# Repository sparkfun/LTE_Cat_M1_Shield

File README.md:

SparkFun LTE CAT M1/NB-IoT Shield - SARA-R4
========================================

[*SparkFun LTE CAT M1/NB-IoT Shield - SARA-R4 (CEL-14997)*](https://www.sparkfun.com/products/14997)

Arduino shield featuring a SARA-R410M-02B module, which supports both Cat M1 and NB-IoT

Repository Contents
-------------------

* **/Documentation** - Data sheets, additional product information
* **/Hardware** - Eagle design files (.brd, .sch)
* **/Production** - Production panel files (.brd)

Documentation
--------------
* **[Installing an Arduino Library Guide](https://learn.sparkfun.com/tutorials/installing-an-arduino-library)** - Basic information on how to install an Arduino library.
* **[Library](https://github.com/sparkfun/SparkFun_LTE_Shield_Arduino_Library)** - Arduino library.
* **[Hookup Guide](https://learn.sparkfun.com/tutorials/lte-cat-m1nb-iot-shield-hookup-guide)** - Basic hookup guide.

Version History
---------------
* v11 - Removed `GND` connection to `AREF` pin
* [v10](https://github.com/sparkfun/LTE_Cat_M1_Shield/releases/tag/v10) - Initial Release

License Information
-------------------

This product is _**open source**_! 

Various bits of the code have different licenses applied. Anything SparkFun wrote is beerware; if you see me (or any other SparkFun employee) at the local, and you've found our code helpful, please buy us a round!

Please use, reuse, and modify these files as you see fit. Please maintain attribution to SparkFun Electronics and release anything derivative under the same license.

Distributed as-is; no warranty is given.

- Your friends at SparkFun.

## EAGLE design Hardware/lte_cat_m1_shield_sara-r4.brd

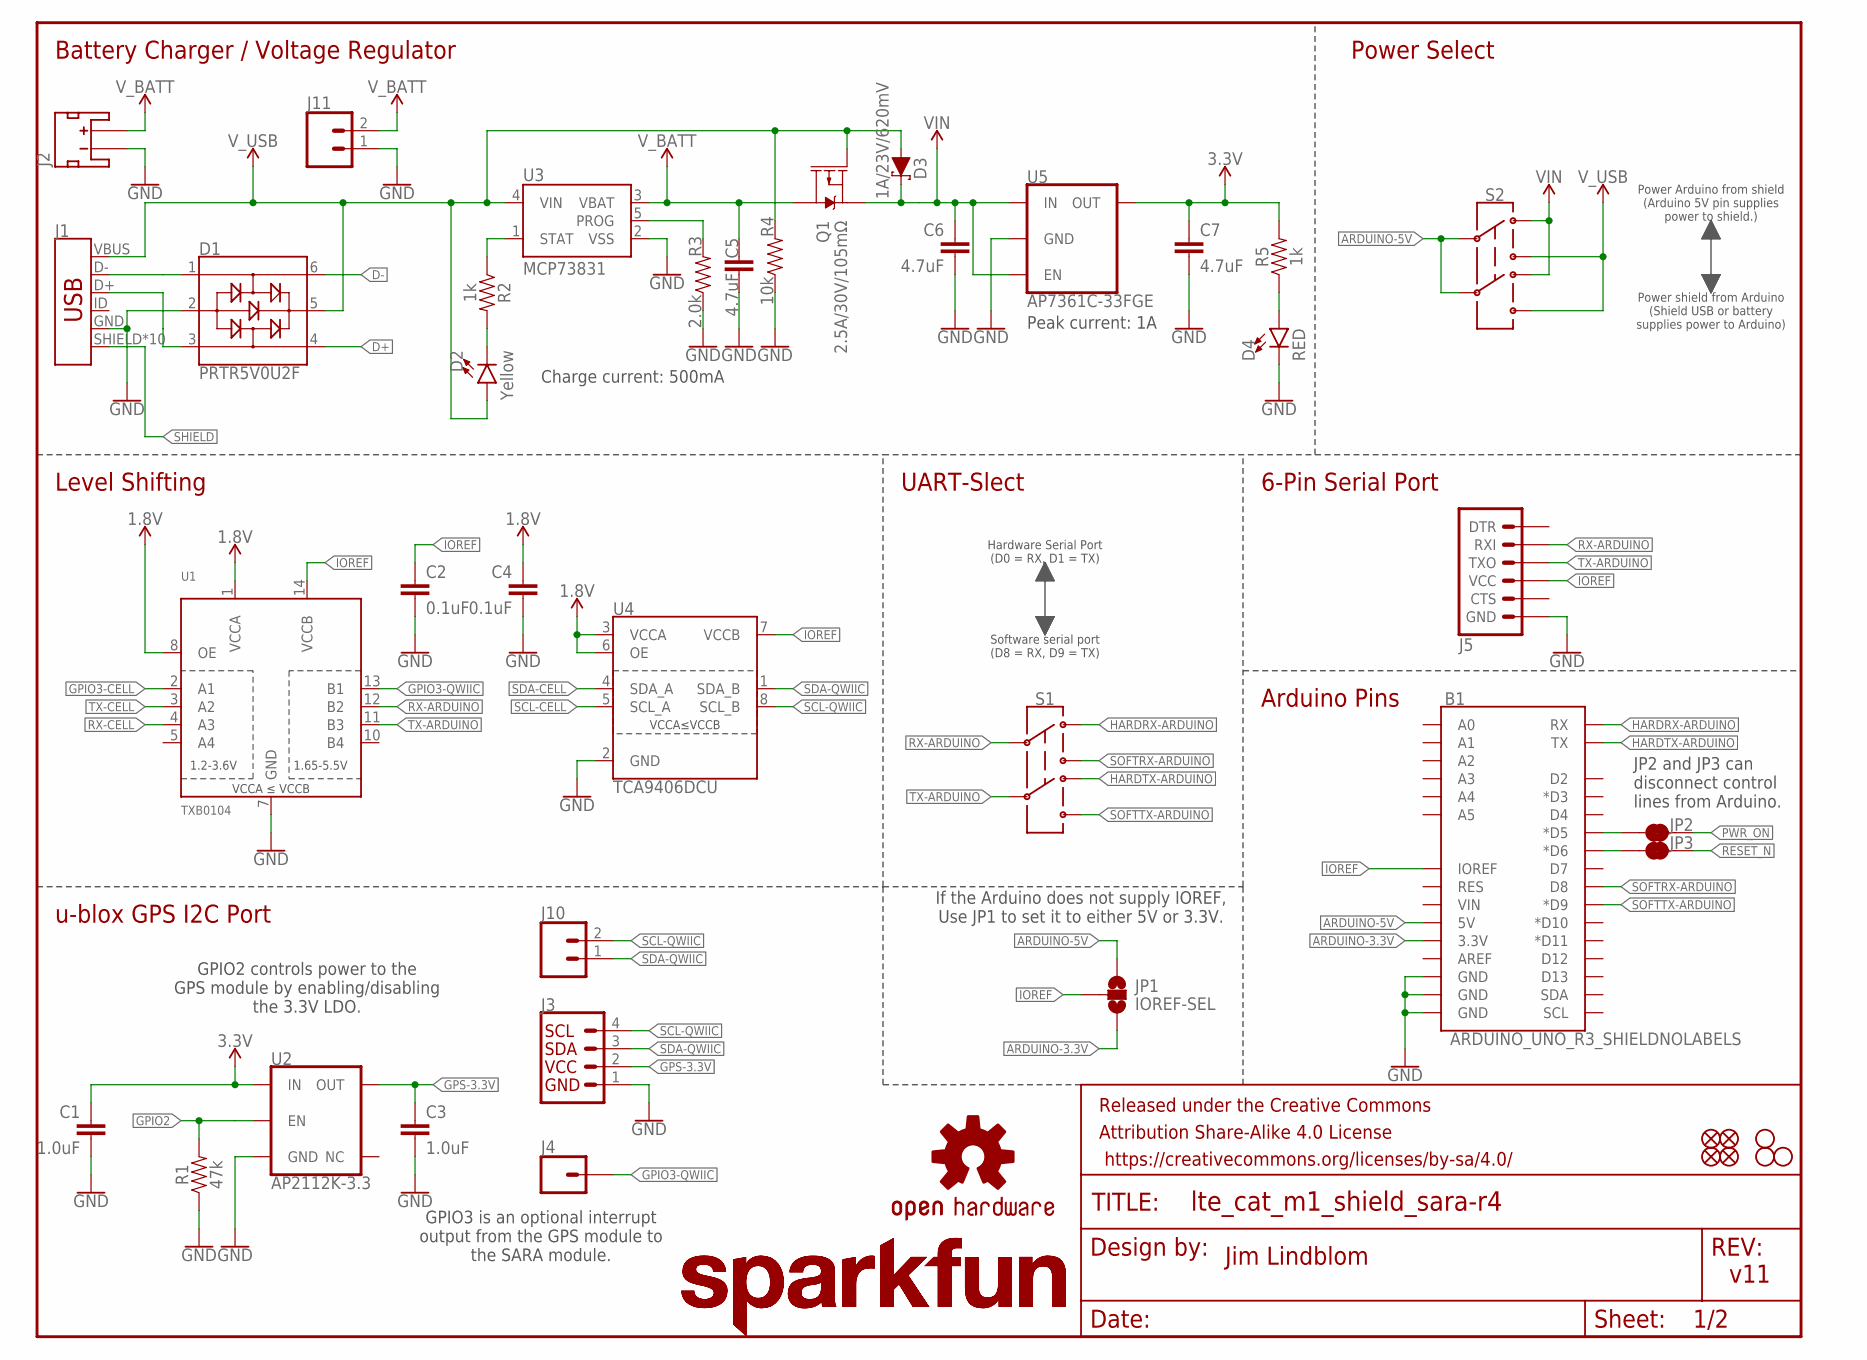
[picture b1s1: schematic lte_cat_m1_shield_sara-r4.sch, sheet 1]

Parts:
B1: ARDUINO_UNO_R3_SHIELDNOLABELS; UNO_R3_SHIELD_NOLABELS
C1, C3: 1.0uF; 0603
C2, C4: 0.1uF; 0603
C5, C6, C7: 4.7uF; 0603
D1: PRTR5V0U2F; SOT886
D2: Yellow; LED-0603
D3: 1A/23V/620mV; SOD-323
D4: RED; LED-0603
FD1, FD2, FD3, FD4: FIDUCIALUFIDUCIAL; FIDUCIAL-MICRO
FRAME1: FRAME-LETTER; CREATIVE_COMMONS
H1, H2, H3: STAND-OFF
J1: USB_MICRO-B_HALF_PTH_MILL; USB-MICROB-PTH-MILL
J2: JST_2MM_MALESMD; JST-2-SMD
J3: QWIIC_CONNECTORJS-1MM; 1X04_1MM_RA
J4: CONN_01PTH_NO_SILK_YES_STOP; 1X01_NO_SILK
J5: 6_PIN_SERIAL_TARGETNO_SILK; 1X06_NO_SILK
J10, J11: CONN_021X02_NO_SILK; 1X02_NO_SILK
JP1: IOREF-SEL; SMT-JUMPER_3_NO_SILK
JP2, JP3: JUMPER-SMT_2_NC_TRACE_SILK; SMT-JUMPER_2_NC_TRACE_SILK
LOGO1, LOGO3: SFE_LOGO_NAME.2_INCH; SFE_LOGO_NAME_.2
LOGO2: OSHW-LOGOM; OSHW-LOGO-M
Q1: 2.5A/30V/105mΩ; SOT23-3
R1: 47k; 0603
R2, R5: 1k; 0603
R3: 2.0k; 0603
R4: 10k; 0603
S1, S2: SWITCH-DPDT-SMD-AYZ0202; SWITCH_DPDT_SMD_AYZ0202
U1: TXB0104; TSSOP14
U2: AP2112K-3.3; SOT23-5
U3: MCP73831; SOT23-5
U4: TCA9406DCU; VSSOP-8
U5: AP7361C-33FGE; 8-UDFN

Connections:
1.8V: C4.1, U1.1 (VCCA), U1.8 (OE), U4.3 (VCCA), U4.6 (OE); also elsewhere on the board
3.3V: C1.1, C7.1, R5.2, U2.1 (IN), U5.1 (OUT); also elsewhere on the board
ARDUINO-3.3V: B1.3.3V, JP1.3
ARDUINO-5V: B1.5V, JP1.1, S2.2, S2.5
D+: D1.4; also elsewhere on the board
D-: D1.6; also elsewhere on the board
GND: B1.GND@0 (GND), B1.GND@1 (GND), B1.GND@2 (GND), C1.2, C2.2, C3.2, C4.2, C5.2, C6.2, C7.2, D1.2, D4.C, J1.GND, J2.1 (-), J3.1, J5.6 (GND), J11.1, R1.1, R3.1, R4.1, U1.7 (GND), U2.2 (GND), U3.2 (VSS), U4.2 (GND), U5.4 (GND), U5.EP (GND); also elsewhere on the board
GPIO2: R1.2, U2.3 (EN); also elsewhere on the board
GPIO3-CELL: U1.2 (A1); also elsewhere on the board
GPIO3-QWIIC: J4.1, U1.13 (B1)
GPS-3.3V: C3.1, J3.2, U2.5 (OUT)
HARDRX-ARDUINO: B1.RX, S1.1
HARDTX-ARDUINO: B1.TX, S1.4
IOREF: B1.IOREF, C2.1, J5.4 (VCC), JP1.2, U1.14 (VCCB), U4.7 (VCCB)
unnamed: R3.2, U3.5 (PROG)
unnamed: D1.1, J1.D-
unnamed: D1.3, J1.D+
unnamed: D4.A, R5.1
unnamed: D2.C, R2.2
unnamed: R2.1, U3.1 (STAT)
unnamed: B1.D5 (*D5), JP2.1
unnamed: B1.D6 (*D6), JP3.1
PWR_ON: JP2.2; also elsewhere on the board
RESET_N: JP3.2; also elsewhere on the board
RX-ARDUINO: J5.2 (RXI), S1.2, U1.12 (B2)
RX-CELL: U1.4 (A3); also elsewhere on the board
SCL-CELL: U4.5 (SCL_A); also elsewhere on the board
SCL-QWIIC: J3.4, J10.2, U4.8 (SCL_B)
SDA-CELL: U4.4 (SDA_A); also elsewhere on the board
SDA-QWIIC: J3.3, J10.1, U4.1 (SDA_B)
SHIELD: J1.SHIELD, J1.SHIELD2 (SHIELD), J1.SHIELD3 (SHIELD), J1.SHIELD4 (SHIELD), J1.SHIELD5 (SHIELD), J1.SHIELD6 (SHIELD), J1.SHIELD7 (SHIELD), J1.SHIELD8 (SHIELD), J1.SHIELD9 (SHIELD), J1.SHIELD10 (SHIELD)
SOFTRX-ARDUINO: B1.D8, S1.3
SOFTTX-ARDUINO: B1.D9 (*D9), S1.6
TX-ARDUINO: J5.3 (TXO), S1.5, U1.11 (B3)
TX-CELL: U1.3 (A2); also elsewhere on the board
VIN: C6.1, D3.C, Q1.2 (S), S2.1, S2.4, U5.5 (EN), U5.8 (IN)
V_BATT: C5.1, J2.2 (+), J11.2, Q1.3 (D), U3.3 (VBAT)
V_USB: D1.5, D2.A, D3.A, J1.VBUS, Q1.1 (G), R4.2, S2.3, S2.6, U3.4 (VIN); also elsewhere on the board

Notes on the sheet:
Charge current: 500mA
Power Arduino from shield (Arduino 5V pin supplies power to shield.)
Power shield from Arduino (Shield USB or battery supplies power to Arduino)
Battery Charger / Voltage Regulator
Power Select
Level Shifting
If the Arduino does not supply IOREF, Use JP1 to set it to either 5V or 3.3V.
u-blox GPS I2C Port
GPIO2 controls power to the GPS module by enabling/disabling the 3.3V LDO.
GPIO3 is an optional interrupt output from the GPS module to the SARA module.
UART-Slect
6-Pin Serial Port
Arduino Pins
Jim Lindblom
v11
Peak current: 1A
Hardware Serial Port (D0 = RX, D1 = TX)
Software serial port (D8 = RX, D9 = TX)
JP2 and JP3 can disconnect control lines from Arduino.

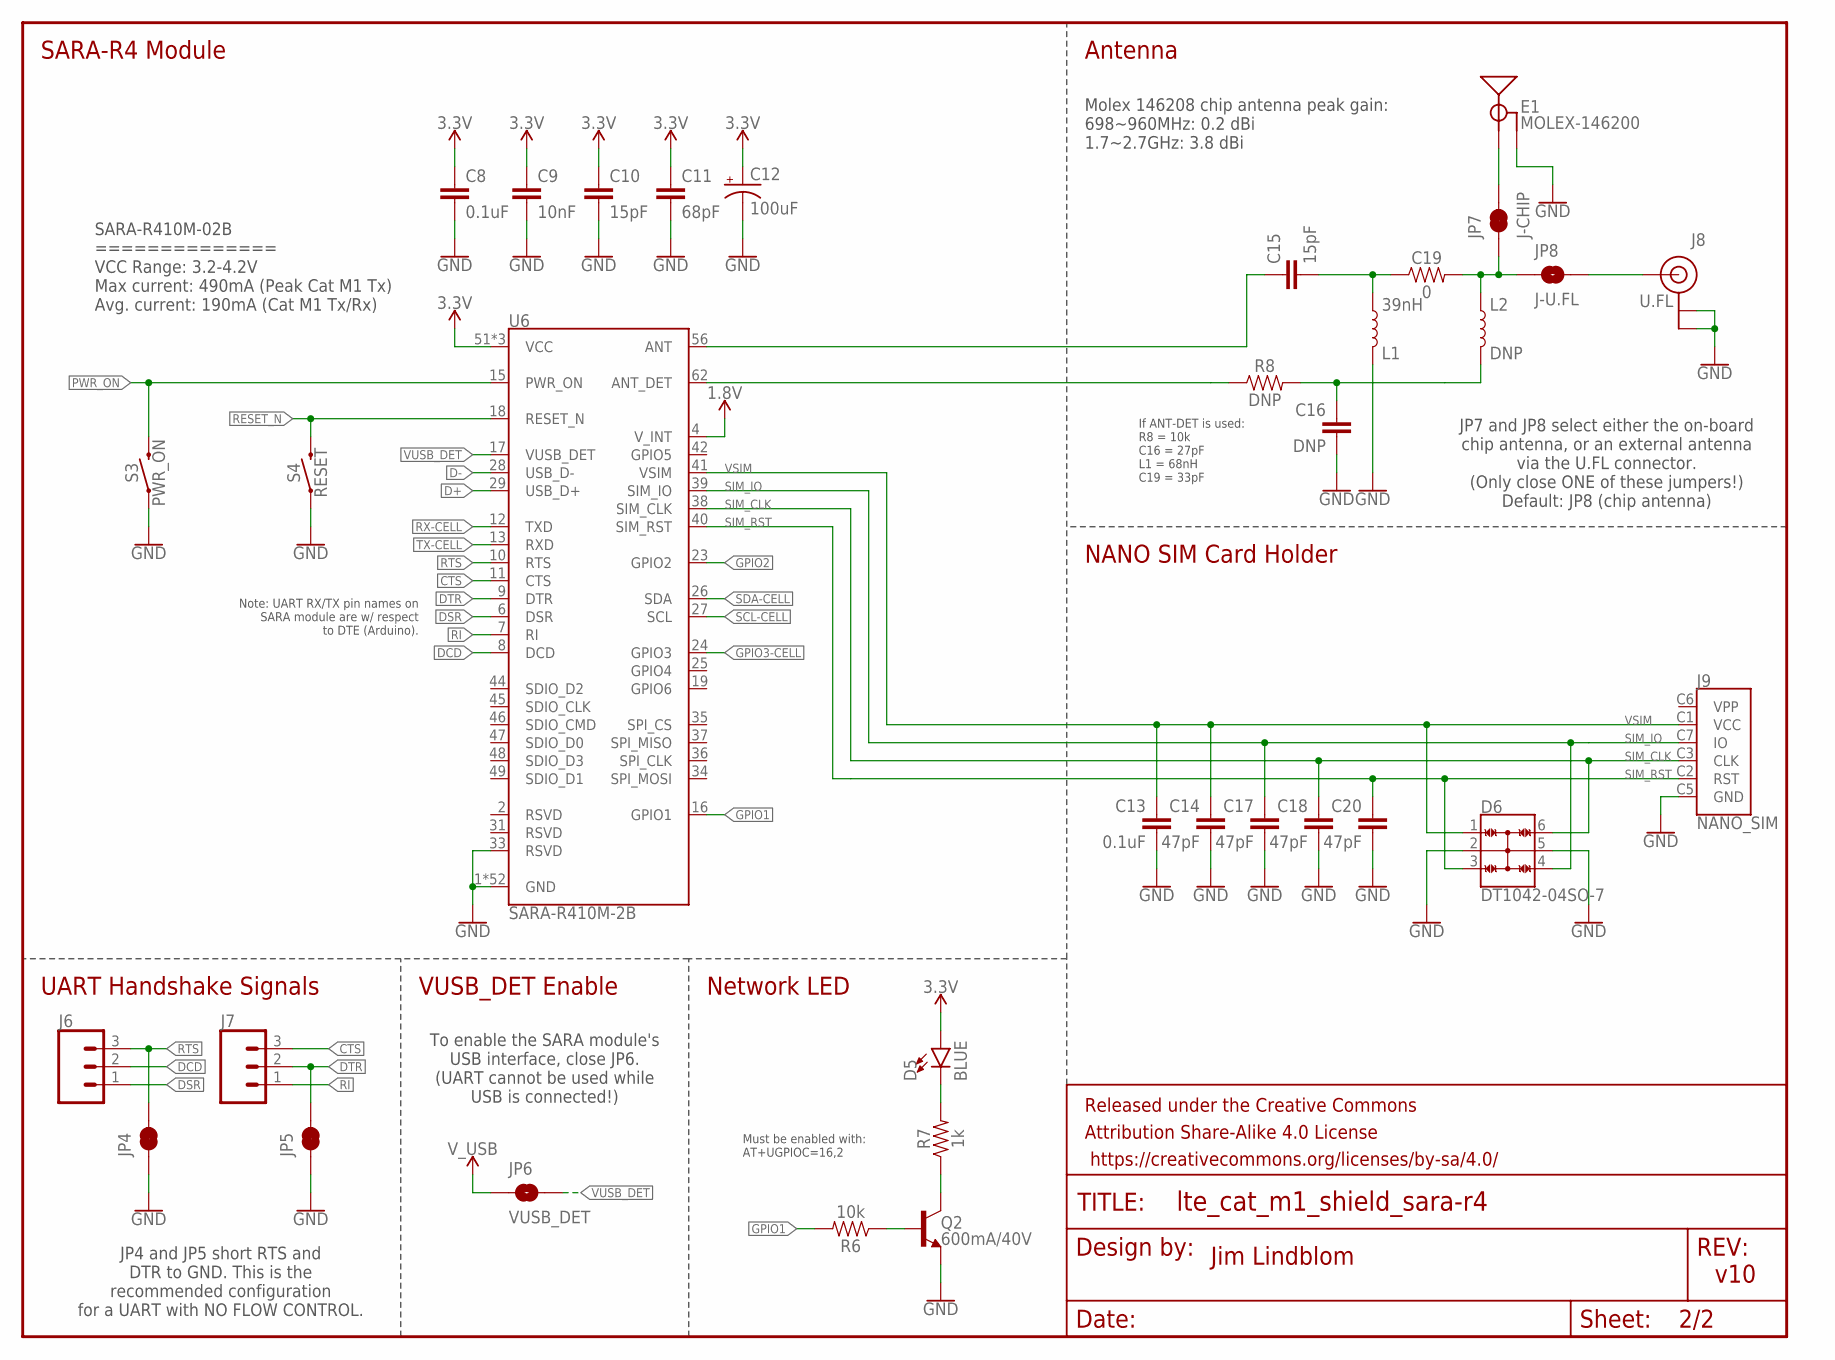
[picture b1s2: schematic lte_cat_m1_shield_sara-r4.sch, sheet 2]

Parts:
C8, C13: 0.1uF; 0603
C9: 10nF; 0603
C10, C15: 15pF; 0603
C11: 68pF; 0603
C12: 100uF; 1206-POLAR
C14, C17, C18, C20: 47pF; 0603
C16: DNP; 0603
C19: 0; 0603
D5: BLUE; LED-0603
D6: DT1042-04SO-7; SOT23-6L
E1: MOLEX-146200; MOLEX_146200
FRAME2: FRAME-LETTER; CREATIVE_COMMONS
J6, J7: CONN_031X03_NO_SILK; 1X03_NO_SILK
J8: U.FL
J9: NANO_SIM; NANO_SIM_WURTH_693043020611
JP4, JP5: JUMPER-SMT_2_NC_TRACE_SILK; SMT-JUMPER_2_NC_TRACE_SILK
JP6: VUSB_DET; SMT-JUMPER_2_NO_SILK
JP7: J-CHIP; SMT-JUMPER_2_NC_TRACE_NO-SILK
JP8: J-U.FL; SMT-JUMPER_2_NO_NO-SILK
L1: 39nH; 0603
L2: DNP; 0603
Q2: 600mA/40V; SOT23-3
R6: 10k; 0603
R7: 1k; 0603
R8: DNP; 0603
S3: PWR_ON; TACTILE_SWITCH_SMD_5.2MM
S4: RESET; TACTILE_SWITCH_SMD_5.2MM
U6: SARA-R410M-2B; SARA-LGA

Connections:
1.8V: U6.4 (V_INT); also elsewhere on the board
3.3V: C8.1, C9.1, C10.1, C11.1, C12.1 (+), D5.A, U6.51 (VCC), U6.52 (VCC), U6.53 (VCC); also elsewhere on the board
ANT: C15.1, U6.56 (ANT)
ANT_DET: R8.1, U6.62 (ANT_DET)
CTS: J7.3, U6.11 (CTS)
D+: U6.29 (USB_D+); also elsewhere on the board
D-: U6.28 (USB_D-); also elsewhere on the board
DCD: J6.2, U6.8 (DCD)
DSR: J6.1, U6.6 (DSR)
DTR: J7.2, JP5.2, U6.9 (DTR)
GND: C8.2, C9.2, C10.2, C11.2, C12.2 (-), C13.2, C14.2, C16.2, C17.2, C18.2, C20.2, D6.2, D6.5, E1.GND, J8.1 (GND), J8.2 (GND), J9.C5 (GND), JP4.1, JP5.1, L1.1, Q2.2 (E), S3.1, S3.2 (1), S4.1, S4.2 (1), U6.1 (GND), U6.3 (GND), U6.5 (GND), U6.14 (GND), U6.20 (GND), U6.21 (GND), U6.22 (GND), U6.30 (GND), U6.32 (GND), U6.33 (RSVD), U6.43 (GND), U6.50 (GND), U6.54 (GND), U6.55 (GND), U6.57 (GND), U6.58 (GND), U6.59 (GND), U6.60 (GND), U6.61 (GND), U6.63 (GND), U6.64 (GND), U6.65 (GND), U6.66 (GND), U6.67 (GND), U6.68 (GND), U6.69 (GND), U6.70 (GND), U6.71 (GND), U6.72 (GND), U6.73 (GND), U6.74 (GND), U6.75 (GND), U6.76 (GND), U6.77 (GND), U6.78 (GND), U6.79 (GND), U6.80 (GND), U6.81 (GND), U6.82 (GND), U6.83 (GND), U6.84 (GND), U6.85 (GND), U6.86 (GND), U6.87 (GND), U6.88 (GND), U6.89 (GND), U6.90 (GND), U6.91 (GND), U6.92 (GND), U6.93 (GND), U6.94 (GND), U6.95 (GND), U6.96 (GND); also elsewhere on the board
GPIO1: R6.2, U6.16 (GPIO1)
GPIO2: U6.23 (GPIO2); also elsewhere on the board
GPIO3-CELL: U6.24 (GPIO3); also elsewhere on the board
unnamed: C16.1, L2.2, R8.2
unnamed: C15.2, C19.1, L1.2
unnamed: J8.FEED (SIGNAL), JP8.2
unnamed: Q2.1 (B), R6.1
unnamed: D5.C, R7.2
unnamed: Q2.3 (C), R7.1
unnamed: C19.2, JP7.1, JP8.1, L2.1
unnamed: E1.FEED (SIGNAL), JP7.2
PWR_ON: S3.3 (2), S3.4 (2), U6.15 (PWR_ON); also elsewhere on the board
RESET_N: S4.3 (2), S4.4 (2), U6.18 (RESET_N); also elsewhere on the board
RI: J7.1, U6.7 (RI)
RTS: J6.3, JP4.2, U6.10 (RTS)
RX-CELL: U6.12 (TXD); also elsewhere on the board
SCL-CELL: U6.27 (SCL); also elsewhere on the board
SDA-CELL: U6.26 (SDA); also elsewhere on the board
SIM_CLK: C18.1, D6.6, J9.C3 (CLK), U6.38 (SIM_CLK)
SIM_IO: C17.1, D6.4, J9.C7 (IO), U6.39 (SIM_IO)
SIM_RST: C20.1, D6.3, J9.C2 (RST), U6.40 (SIM_RST)
TX-CELL: U6.13 (RXD); also elsewhere on the board
VSIM: C13.1, C14.1, D6.1, J9.C1 (VCC), U6.41 (VSIM)
VUSB_DET: JP6.2, U6.17 (VUSB_DET)
V_USB: JP6.1; also elsewhere on the board

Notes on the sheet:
Antenna
SARA-R4 Module
UART Handshake Signals
VUSB_DET Enable
Network LED
To enable the SARA module's USB interface, close JP6. (UART cannot be used while USB is connected!)
JP4 and JP5 short RTS and DTR to GND. This is the recommended configuration for a UART with NO FLOW CONTROL.
NANO SIM Card Holder
JP7 and JP8 select either the on-board chip antenna, or an external antenna via the U.FL connector. (Only close ONE of these jumpers!) Default: JP8 (chip antenna)
Note: UART RX/TX pin names on SARA module are w/ respect to DTE (Arduino).
Molex 146208 chip antenna peak gain: 698~960MHz: 0.2 dBi 1.7~2.7GHz: 3.8 dBi
Jim Lindblom
v10
Must be enabled with: AT+UGPIOC=16,2
SARA-R410M-02B ============== VCC Range: 3.2-4.2V Max current: 490mA (Peak Cat M1 Tx) Avg. current: 190mA (Cat M1 Tx/Rx)
If ANT-DET is used: R8 = 10k C16 = 27pF L1 = 68nH C19 = 33pF

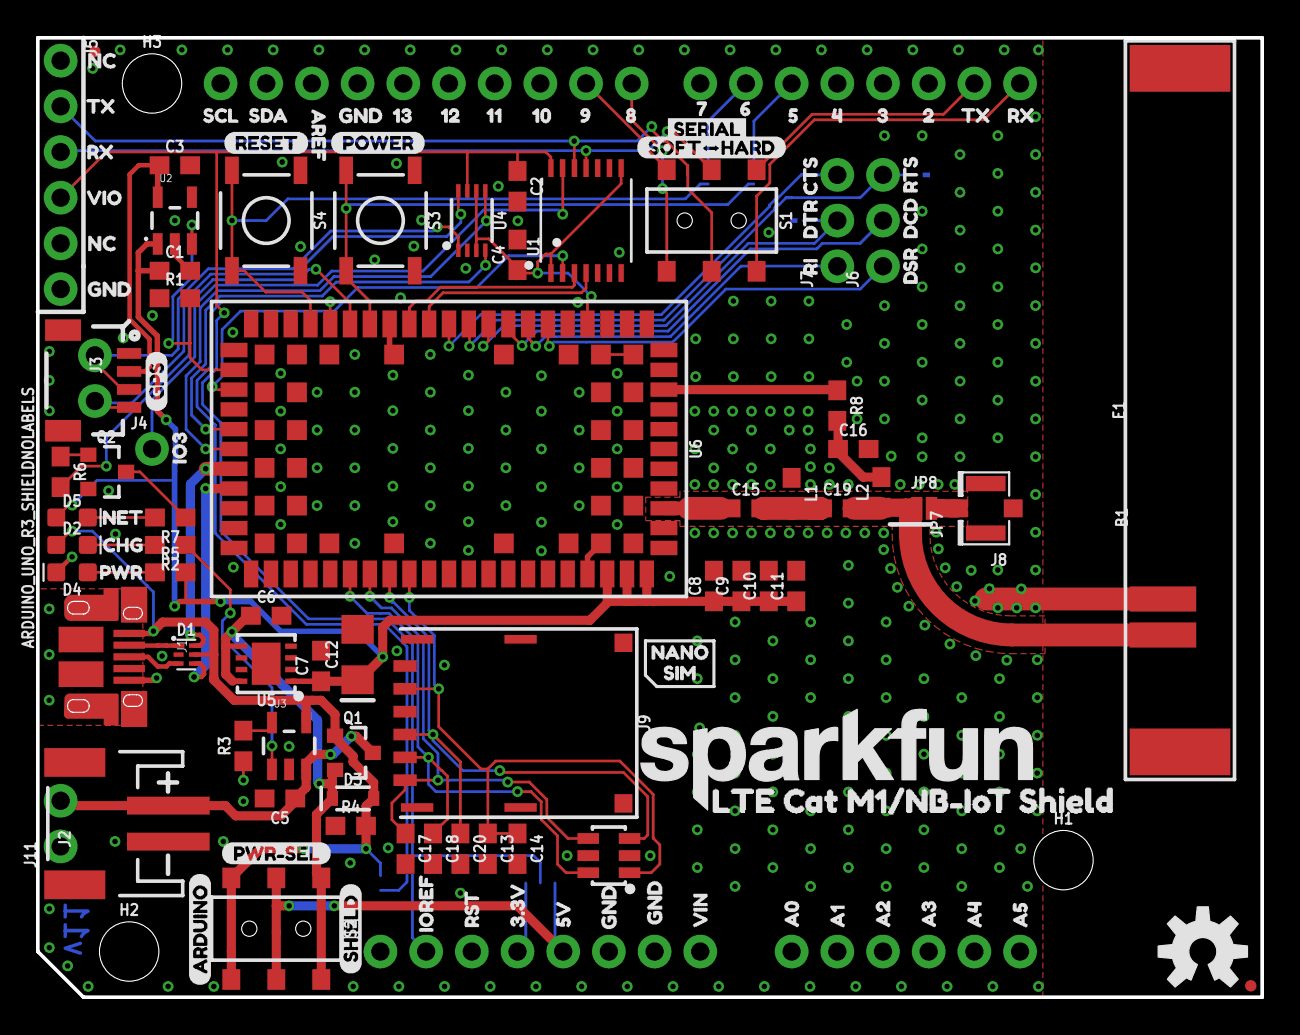
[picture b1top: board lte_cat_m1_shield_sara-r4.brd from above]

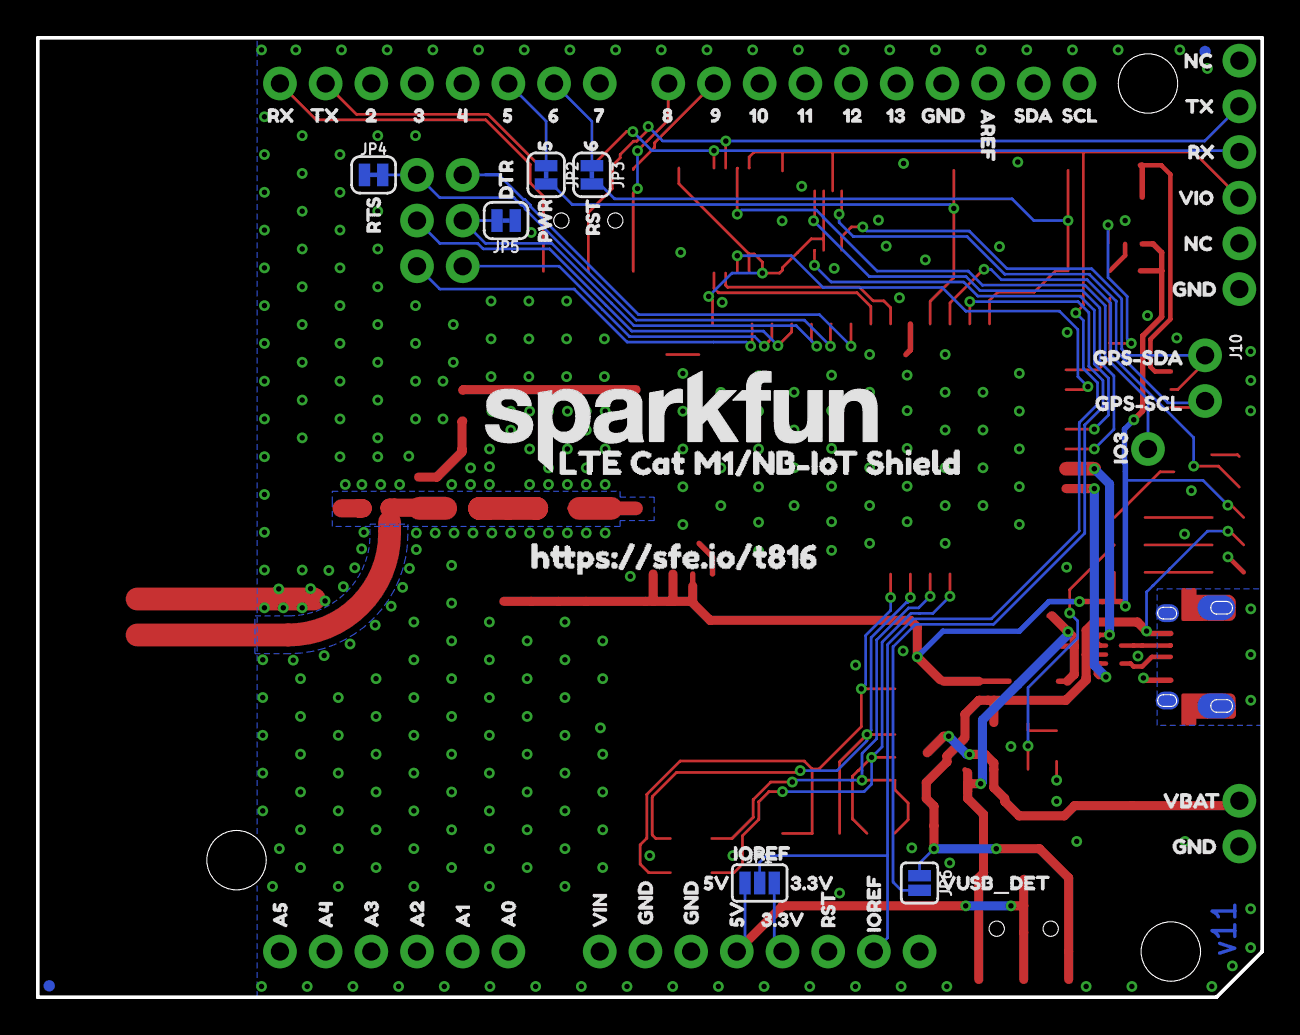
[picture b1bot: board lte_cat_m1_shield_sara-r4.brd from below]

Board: 2 copper layers, 68.1 x 53.3 mm, 193 parts (64 on the bottom side), 60 nets.

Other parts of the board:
U$1, U$85: SCL0
U$2, U$84: SDA1
U$3, U$86: AREF2
U$4, U$45, U$46, U$73, U$74, U$88, U$104, U$105, U$112: GND3
U$5, U$87: 134
U$6, U$89: 125
U$7, U$90: 116
U$8, U$91: 107
U$9, U$92: 98
U$10, U$93: 89
U$11: RESET48
U$12: GPS47
U$13, U$94: 714
U$14, U$62, U$95: 615
U$15, U$61, U$96: 516
U$16, U$97: 417
U$17, U$98: 318
U$18, U$99: 219
U$19: POWER49
U$20, U$30, U$81, U$101: RX22
U$21, U$31, U$80, U$100: TX21
U$22: SERIAL57
U$23: CTS23
U$24, U$63: DTR24
U$25: RI25
U$26: DSR26
U$27: DCD27
U$28, U$64: RTS28
U$29, U$82: VIO29
U$32, U$77: LTE_CAT_M1#NB#IOT_SHIELD1
U$33: ARDUINO51
U$34, U$79: IO334
U$35: NET31
U$36: CHG33
U$37, U$59: PWR32
U$38: PWR#SEL53
U$39: SHIELD52
U$40, U$42: RST0
U$41, U$56, U$78: IOREF39
U$43, U$58, U$76: 3#3V41
U$44, U$57, U$75: 5V42
U$47, U$72: VIN43
U$48, U$71: A044
U$49, U$70: A145
U$50, U$69: A246
U$51, U$68: A347
U$52, U$67: A448
U$53, U$66: A549
U$54: NANO50
U$55: SIM51
U$60: RST40
U$65: VUSB_DET52
U$83: HTTPS###SFE#IO#T8160
U$102: SOFT#HARD50
U$103, U$106, U$107, U$108: NC0
U$109: GPS#SCL1
U$110: GPS#SDA0
U$111: VBAT2

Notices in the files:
parts and their libraries:
SparkFun-Aesthetics: Licensing: Creative Commons ShareAlike 4.0 International - https://creativecommons.org/licenses/by-sa/4.0
SparkFun-Aesthetics: Released under the Creative Commons Attribution Share-Alike 4.0 License
SparkFun-Aesthetics: https://creativecommons.org/licenses/by-sa/4.0
